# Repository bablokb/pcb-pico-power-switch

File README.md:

Pico Power Switch
=================

This is a simple breakout to switch the battery power for a Raspberry
Pi Pico to minimize battery usage.

Functions:

  * Enable using a button, a RTC or an external signal
  * Disable by pulling a GPIO high from your program
  * keep time

The target application of this design is a program that runs in
intervals. After startup the program executes it's tasks, sets the
next wakup time and then pulls the "done"-GPIO high.  The circuitry
then cuts power, thus limiting the battery consumption to a very low
level. Measured current draw in off-mode is about 0.35µA.

The design of the breakout allows it to be connected directly on the bottom
side of the Pico.

Hardware Components
-------------------

A D-type flip-flop drives the gate of a p-channel mosfet and
switches power (source: battery, drain: VSYS). 
A button, the RTC or an external signal will reset the flip-flop.
This will pull the gate low, thus enabling power.

The "done"-pin of the Pico is connected to the CLK-pin of
the flip-flop. A rising edge will toggle the output and pull
the gate high, which in turn cuts power.

A second p-channel mosfet will prevent back-powering from VBUS
in case the Pico is connected using the USB-connector. The
voltage-drop across this mosfet is about 0.1V.

PCB
---

PCB design files are in `pico-power-switch.kicad`.

Ready to use production files for JLCPCB are in `production_files`.

Software
--------

A simple example program implemented in CircuitPython
is provided in `src/main.py`. The software provides some boilerplate
code for timer and alarm-based wake up.

In timer-mode, the program uses the countdown-timer of the rtc. It
blinks the on-board LED for ten seconds, then goes to sleep for 15 seconds.

For longer intervals alarm-based wake up is more suitable. Since the rtc
does not support seconds for alarms, it will always fire on "full minutes".

Measured current
----------------

Using a Nordic-PPK2, a Pico-W running with 3.6V draws an average
current of 0.35µA:

License
-------

[![CC BY-SA 4.0][cc-by-sa-shield]][cc-by-sa]

This work is licensed under a
[Creative Commons Attribution-ShareAlike 4.0 International
License][cc-by-sa].

[![CC BY-SA 4.0][cc-by-sa-image]][cc-by-sa]

[cc-by-sa]: http://creativecommons.org/licenses/by-sa/4.0/
[cc-by-sa-image]: https://licensebuttons.net/l/by-sa/4.0/88x31.png
[cc-by-sa-shield]:
https://img.shields.io/badge/License-CC%20BY--SA%204.0-lightgrey.svg

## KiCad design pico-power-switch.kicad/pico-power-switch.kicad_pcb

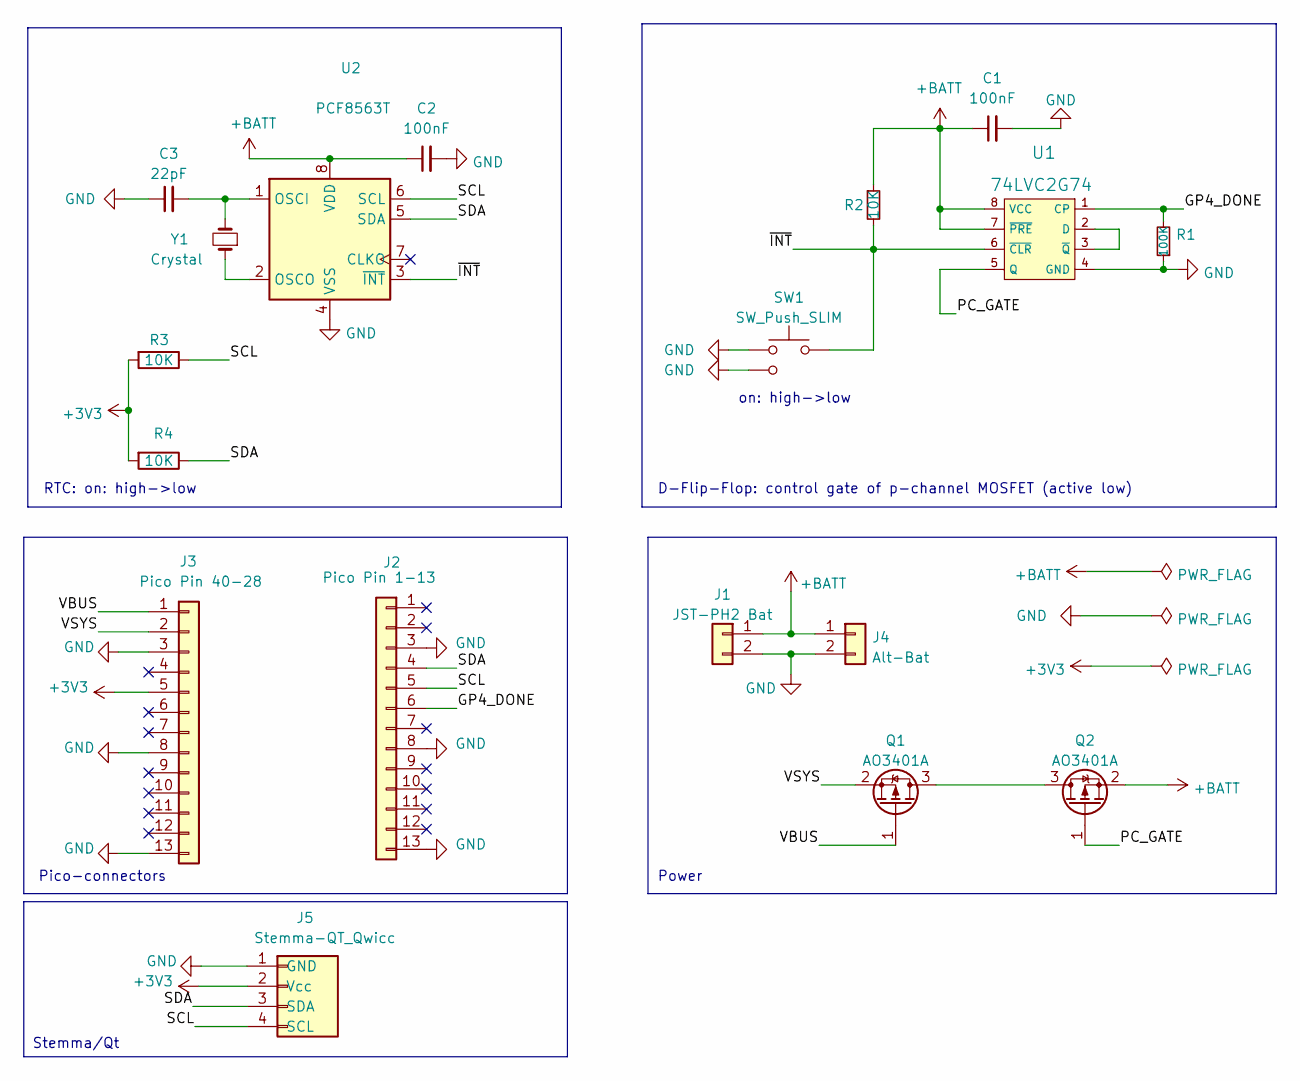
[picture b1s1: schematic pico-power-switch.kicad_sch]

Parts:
C1, C2: 100nF; C_0402_1005Metric; LCSC C1525
C3: 22pF; C_0402_1005Metric; LCSC C1555
J1: JST-PH2 Bat; JST_PH_S2B-PH-SM4-TB_1x02-1MP_P2.00mm_Horizontal
J2: Pico Pin 1-13; PinHeader_1x13_P2.54mm_Vertical
J3: Pico Pin 40-28; PinHeader_1x13_P2.54mm_Vertical
J4: Alt-Bat; PinHeader_1x02_P2.54mm_Vertical
J5: Stemma-QT_Qwicc; JST_SH_SM04B-SRSS-TB_1x04-1MP_P1.00mm_Horizontal
Q1, Q2: AO3401A; SOT-23; LCSC C15127
R1: 100K; R_0402_1005Metric; LCSC C25741
R2, R3, R4: 10K; R_0402_1005Metric; LCSC C25744
SW1: SW_Push_SLIM; SW_PUSH_SLIM_1x4
U1: 74LVC2G74; TSSOP-8_3x3mm_P0.65mm; MPN SN74HC74N; Digi-Key_PN 296-1602-5-ND
U2: PCF8563T; SOIC-8_3.9x4.9mm_P1.27mm; LCSC C7440
Y1: Crystal; Crystal_SMD_3215-2Pin_3.2x1.5mm; LCSC C32346

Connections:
+3V3: J3.5, J5.2 (Vcc), R3.2, R4.2
+BATT: C1.1, C2.1, J1.1, J4.1, Q2.2 (S), R2.1, U1.7 (~PRE), U1.8 (VCC), U2.8 (VDD)
/GP4_DONE: J2.6, R1.2, U1.1 (CP)
/PC_GATE: Q2.1 (G), U1.5 (Q)
/SCL: J2.5, J5.4 (SCL), R3.1, U2.6 (SCL)
/SDA: J2.4, J5.3 (SDA), R4.1, U2.5 (SDA)
/VBUS: J3.1, Q1.1 (G)
/VSYS: J3.2, Q1.2 (S)
/~INT: R2.2, SW1.2, U1.6 (~CLR), U2.3 (~INT)
GND: C1.2, C2.2, C3.1, J1.2, J2.3, J2.8, J2.13, J3.3, J3.8, J3.13, J4.2, J5.1 (GND), R1.1, SW1.1, SW1.3 (1), U1.4 (GND), U2.4 (VSS)
unnamed: C3.2, U2.1 (OSCI), Y1.2
unnamed: Q1.3 (D), Q2.3 (D)
unnamed: U1.2 (D), U1.3 (~Q)
unnamed: U2.2 (OSCO), Y1.1

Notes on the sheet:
Power
D-Flip-Flop: control gate of p-channel MOSFET (active low)
Pico-connectors
RTC: on: high->low
Stemma/Qt
on: high->low

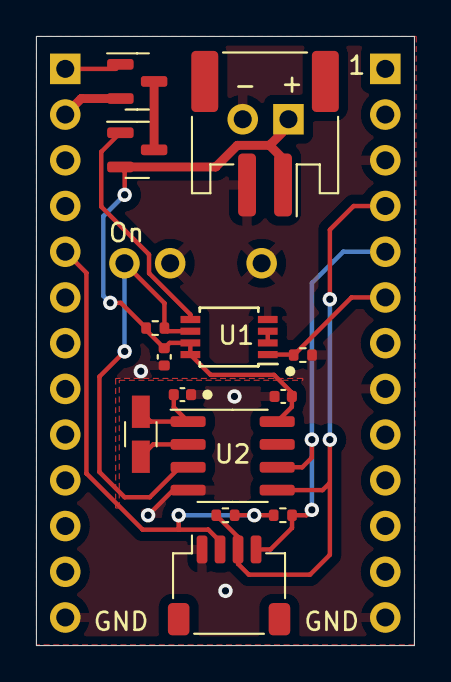
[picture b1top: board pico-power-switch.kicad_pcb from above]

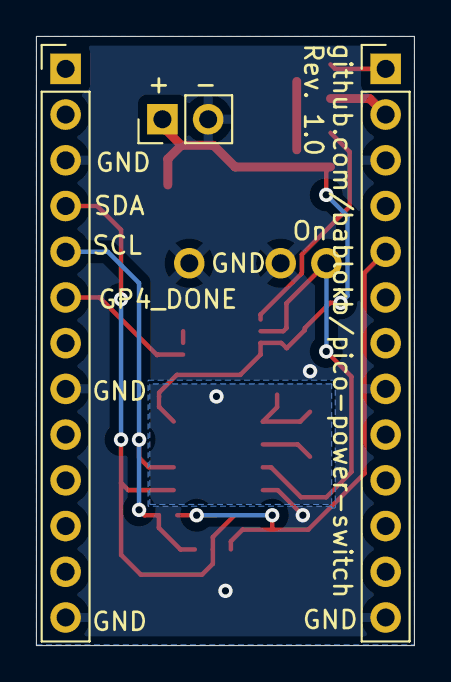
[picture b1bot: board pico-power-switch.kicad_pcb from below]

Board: 2 copper layers, 21.0 x 33.8 mm, 18 parts (3 on the bottom side), 14 nets.

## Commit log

2023-06-10 Rev 1.0 (in production)
2023-06-20 fixed schematic for power-connectors
2023-07-11 added some details
2023-07-15 added example program
2024-06-03 added image of the PCB
2024-06-03 updated information
2024-06-29 document current measurement
